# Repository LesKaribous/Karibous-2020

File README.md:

# Karibous-2020
Sources des projets robotique des Karibous pour l'année 2020

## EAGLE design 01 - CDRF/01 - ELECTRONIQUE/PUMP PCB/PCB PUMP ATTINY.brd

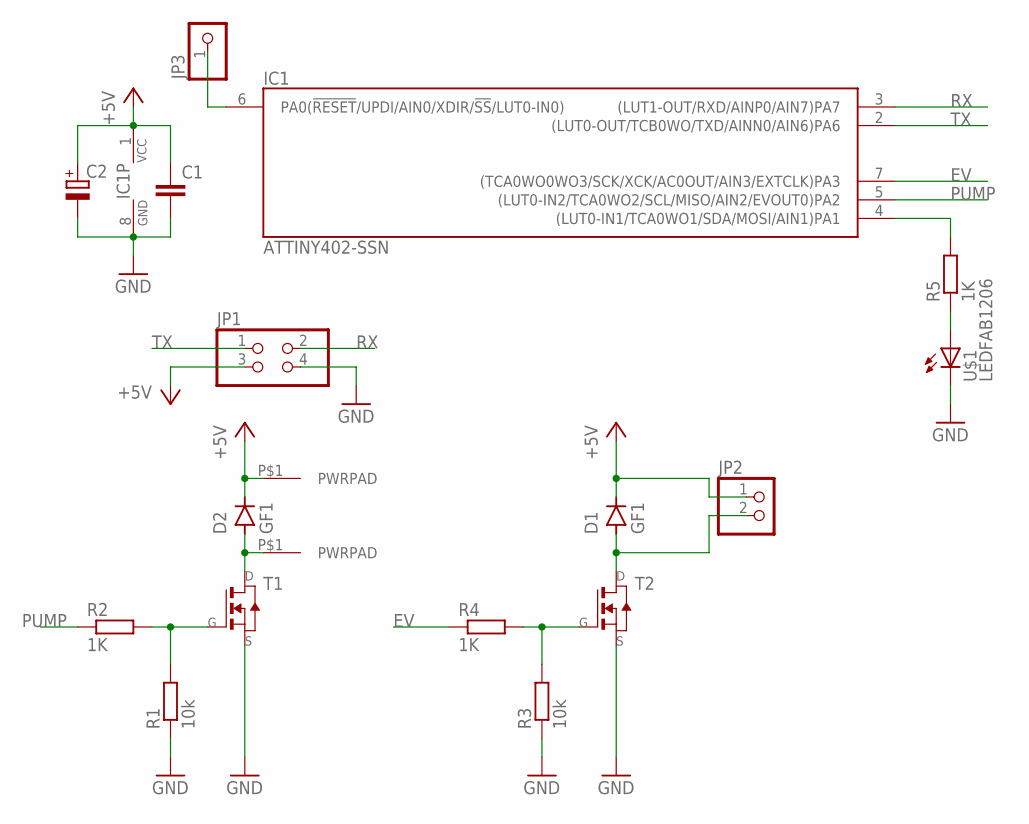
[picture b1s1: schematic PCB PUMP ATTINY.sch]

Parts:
C1: C-EUC1206; C1206
C2: CPOL-EU153CLV-0505; 153CLV-0505
D1, D2: GF1; SMA-DO214AC
IC1: ATTINY402-SSN; SO8
J3, J4: PWRPAD2-5MM; PWRPAD_2-5MM
JP1: PINHD-2X02_2.54-SMD; 2X02SMD
JP2: PINHD-1X02_2.54-SMD-90°; 1X02SMD/90
JP3: PINHD-1X01_2.54-SMD; 1X01SMD
R1, R3: 10k; R1206
R2, R4, R5: 1K; R1206
T1, T2: NMOSFETSOT23; SOT-23
U$1: LEDFAB1206; LED1206FAB

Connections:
+5V: C1.1, C2.+, D1.K (C), D2.K (C), IC1.1 (VCC), J4.P$1, JP1.3, JP2.1
EV: IC1.7 ((TCA0WO0WO3/SCK/XCK/AC0OUT/AIN3/EXTCLK)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), R4.1
GND: C1.2, C2.-, IC1.8 (GND), JP1.4, R1.1, R3.1, T1.2 (S), T2.2 (S), U$1.2 (C)
unnamed: D1.A, JP2.2, T2.1 (D)
unnamed: D2.A, J3.P$1, T1.1 (D)
unnamed: R1.2, R2.2, T1.3 (G)
unnamed: R3.2, R4.2, T2.3 (G)
unnamed: IC1.6 (PA0(!RESET!/UPDI/AIN0/XDIR/!SS!/LUT0-IN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), JP3.1
unnamed: R5.1, U$1.1 (A)
unnamed: IC1.4 ((LUT0-IN1/TCA0WO1/SDA/MOSI/AIN1)PA1), R5.2
PUMP: IC1.5 ((LUT0-IN2/TCA0WO2/SCL/MISO/AIN2/EVOUT0)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), R2.1
RX: IC1.3 ((LUT1-OUT/RXD/AINP0/AIN7)PA7), JP1.2
TX: IC1.2 ((LUT0-OUT/TCB0WO/TXD/AINN0/AIN6)PA6), JP1.1

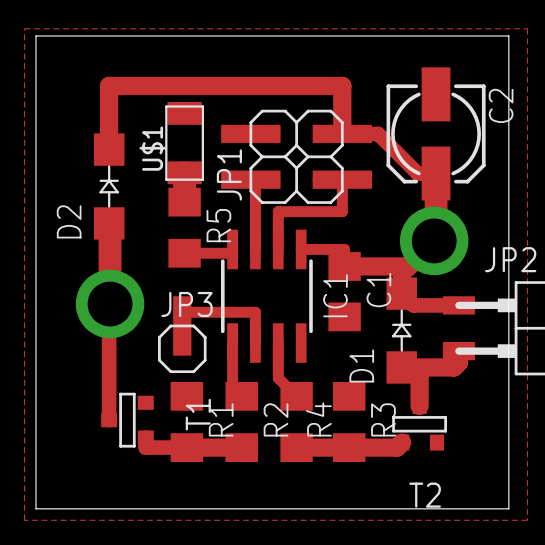
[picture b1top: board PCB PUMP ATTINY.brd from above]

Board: 2 copper layers, 26.3 x 26.3 mm, 18 parts (0 on the bottom side), 13 nets.

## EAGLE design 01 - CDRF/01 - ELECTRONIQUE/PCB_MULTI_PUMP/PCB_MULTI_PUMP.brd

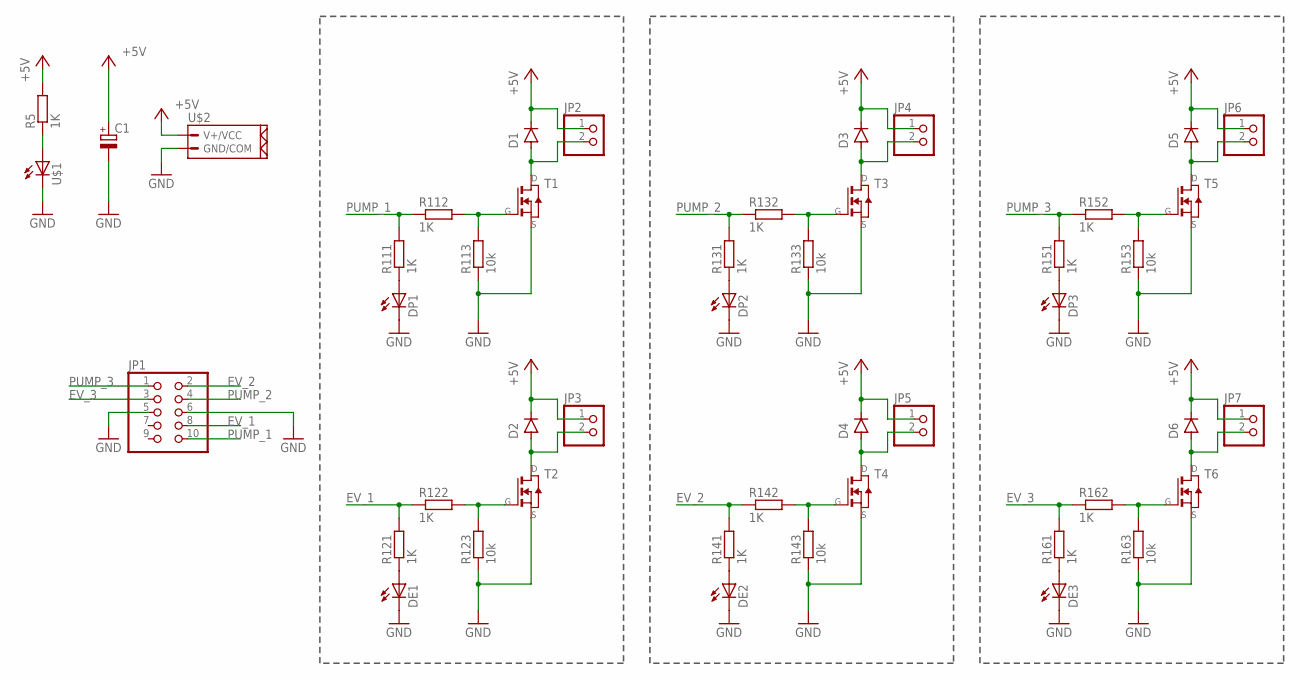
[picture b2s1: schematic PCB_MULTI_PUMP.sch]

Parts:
C1: CPOL-EUE5-10.5; E5-10,5
D1, D2, D3, D4, D5, D6: GF1; SMA-DO214AC
DE1, DE2, DE3: LEDFAB1206; LED1206FAB
DP1, DP2, DP3: LEDFAB1206; LED1206FAB
JP1: PINHD-2X05_2.54-SMD; 2X05SMD
JP2, JP3, JP4, JP5, JP6, JP7: PINHD-1X02_2.54-SMD-90°; 1X02SMD/90
R5, R111, R112, R121, R122, R131, R132, R141, R142, R151, R152, R161, R162: 1K; R1206
R113, R123, R133, R143, R153, R163: 10k; R1206
T1, T2, T3, T4, T5, T6: NMOSFETSOT23; SOT-23
U$1: LEDFAB1206; LED1206FAB
U$2: CONN_02_PUI; NSK396-2C

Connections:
+5V: C1.+, D1.K (C), D2.K (C), D3.K (C), D4.K (C), D5.K (C), D6.K (C), JP2.1, JP3.1, JP4.1, JP5.1, JP6.1, JP7.1, R5.2, U$2.P$2 (V+/VCC)
EV_1: JP1.8, R121.2, R122.1
EV_2: JP1.2, R141.2, R142.1
EV_3: JP1.3, R161.2, R162.1
GND: C1.-, DE1.2 (C), DE2.2 (C), DE3.2 (C), DP1.2 (C), DP2.2 (C), DP3.2 (C), JP1.5, JP1.6, R113.1, R123.1, R133.1, R143.1, R153.1, R163.1, T1.2 (S), T2.2 (S), T3.2 (S), T4.2 (S), T5.2 (S), T6.2 (S), U$1.2 (C), U$2.P$1 (GND/COM)
unnamed: D2.A, JP3.2, T2.1 (D)
unnamed: D1.A, JP2.2, T1.1 (D)
unnamed: R112.2, R113.2, T1.3 (G)
unnamed: R122.2, R123.2, T2.3 (G)
unnamed: R5.1, U$1.1 (A)
unnamed: DP1.1 (A), R111.1
unnamed: DE1.1 (A), R121.1
unnamed: D3.A, JP4.2, T3.1 (D)
unnamed: R132.2, R133.2, T3.3 (G)
unnamed: D4.A, JP5.2, T4.1 (D)
unnamed: R142.2, R143.2, T4.3 (G)
unnamed: DP2.1 (A), R131.1
unnamed: DE2.1 (A), R141.1
unnamed: D5.A, JP6.2, T5.1 (D)
unnamed: R152.2, R153.2, T5.3 (G)
unnamed: D6.A, JP7.2, T6.1 (D)
unnamed: R162.2, R163.2, T6.3 (G)
unnamed: DP3.1 (A), R151.1
unnamed: DE3.1 (A), R161.1
PUMP_1: JP1.10, R111.2, R112.1
PUMP_2: JP1.4, R131.2, R132.1
PUMP_3: JP1.1, R151.2, R152.1

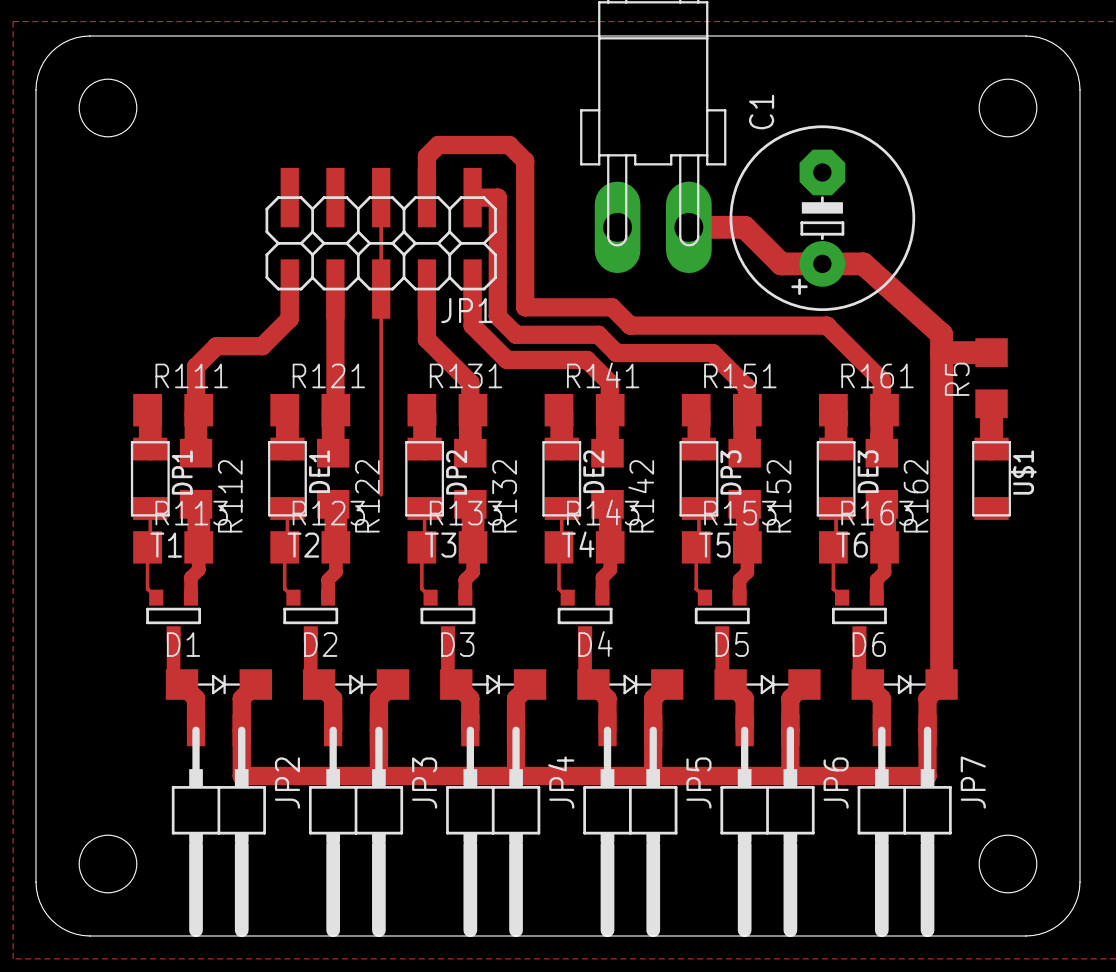
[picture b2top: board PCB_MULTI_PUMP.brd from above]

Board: 2 copper layers, 58.0 x 50.0 mm, 47 parts (0 on the bottom side), 27 nets.

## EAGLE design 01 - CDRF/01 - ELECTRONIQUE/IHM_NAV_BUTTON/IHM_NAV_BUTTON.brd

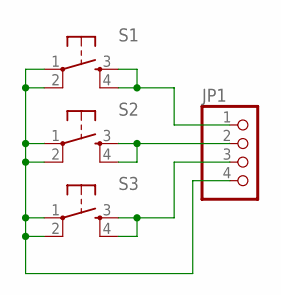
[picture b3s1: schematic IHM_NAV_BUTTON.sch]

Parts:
JP1: PINHD-1X04_2.54-SMD-90°; 1X04SMD/90
S1, S2, S3: 6MM_SWITCH6MM_SWITCH; 6MM_SWITCH

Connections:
unnamed: JP1.1, S1.3 (S), S1.4 (S1)
unnamed: JP1.2, S2.3 (S), S2.4 (S1)
unnamed: JP1.3, S3.3 (S), S3.4 (S1)
unnamed: JP1.4, S1.1, S1.2 (P1), S2.1, S2.2 (P1), S3.1, S3.2 (P1)

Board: 2 copper layers, 4 parts (0 on the bottom side), 4 nets, no tracks yet.

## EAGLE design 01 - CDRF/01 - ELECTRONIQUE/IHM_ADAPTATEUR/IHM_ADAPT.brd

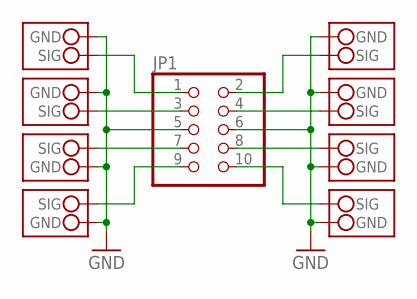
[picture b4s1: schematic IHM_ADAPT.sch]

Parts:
JP1: PINHD-2X05_2.54-SMD; 2X05SMD
U$1, U$2, U$3, U$4, U$5, U$6, U$7, U$8: CONN_WIRE; SMD_WIRE_CON

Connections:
GND: JP1.5, JP1.6, U$1.P$1 (GND), U$2.P$1 (GND), U$3.P$1 (GND), U$4.P$1 (GND), U$5.P$1 (GND), U$6.P$1 (GND), U$7.P$1 (GND), U$8.P$1 (GND)
unnamed: JP1.10, U$4.P$2 (SIG)
unnamed: JP1.8, U$2.P$2 (SIG)
unnamed: JP1.4, U$1.P$2 (SIG)
unnamed: JP1.2, U$3.P$2 (SIG)
unnamed: JP1.9, U$8.P$2 (SIG)
unnamed: JP1.7, U$6.P$2 (SIG)
unnamed: JP1.3, U$5.P$2 (SIG)
unnamed: JP1.1, U$7.P$2 (SIG)

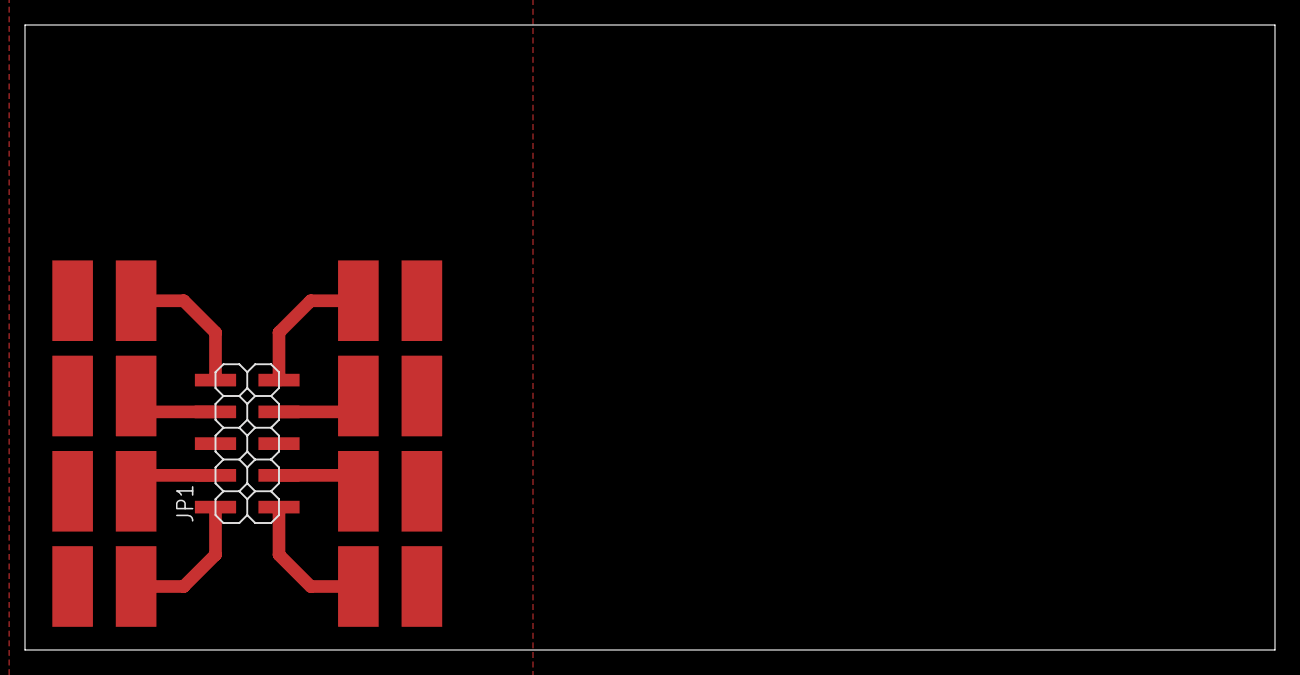
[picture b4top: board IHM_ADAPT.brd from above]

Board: 2 copper layers, 100.0 x 50.0 mm, 9 parts (0 on the bottom side), 9 nets.

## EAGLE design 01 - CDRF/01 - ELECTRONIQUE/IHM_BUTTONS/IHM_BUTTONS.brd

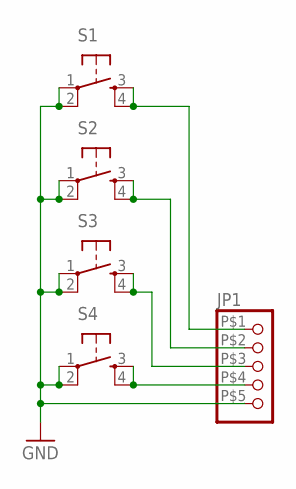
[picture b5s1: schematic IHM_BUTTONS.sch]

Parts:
JP1: PINHD-1X05_2.54-SMD-WIRE; 1X05WIRE
S1, S2, S3, S4: 6MM_SWITCH6MM_SWITCH; 6MM_SWITCH

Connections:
GND: JP1.P$5 (5), S1.1, S1.2 (P1), S2.1, S2.2 (P1), S3.1, S3.2 (P1), S4.1, S4.2 (P1)
unnamed: JP1.P$4 (4), S4.3 (S), S4.4 (S1)
unnamed: JP1.P$3 (3), S3.3 (S), S3.4 (S1)
unnamed: JP1.P$2 (2), S2.3 (S), S2.4 (S1)
unnamed: JP1.P$1 (1), S1.3 (S), S1.4 (S1)

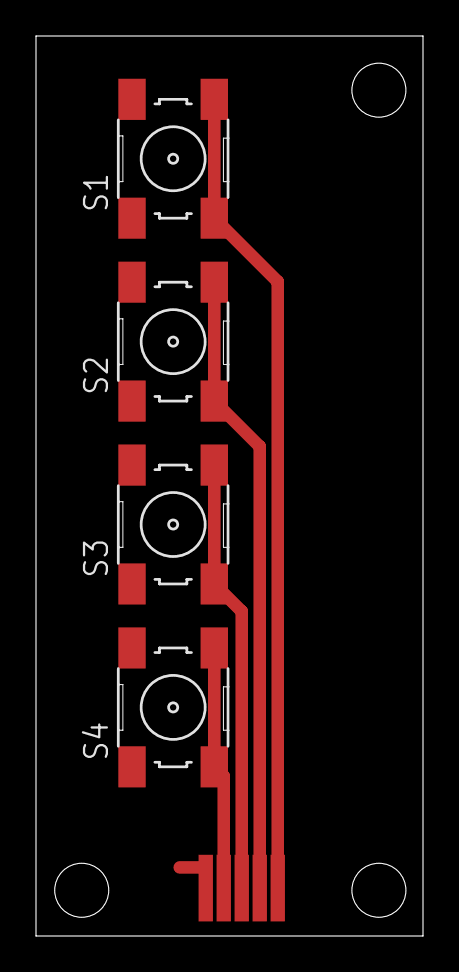
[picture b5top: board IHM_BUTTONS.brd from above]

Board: 2 copper layers, 21.5 x 50.0 mm, 5 parts (0 on the bottom side), 5 nets.

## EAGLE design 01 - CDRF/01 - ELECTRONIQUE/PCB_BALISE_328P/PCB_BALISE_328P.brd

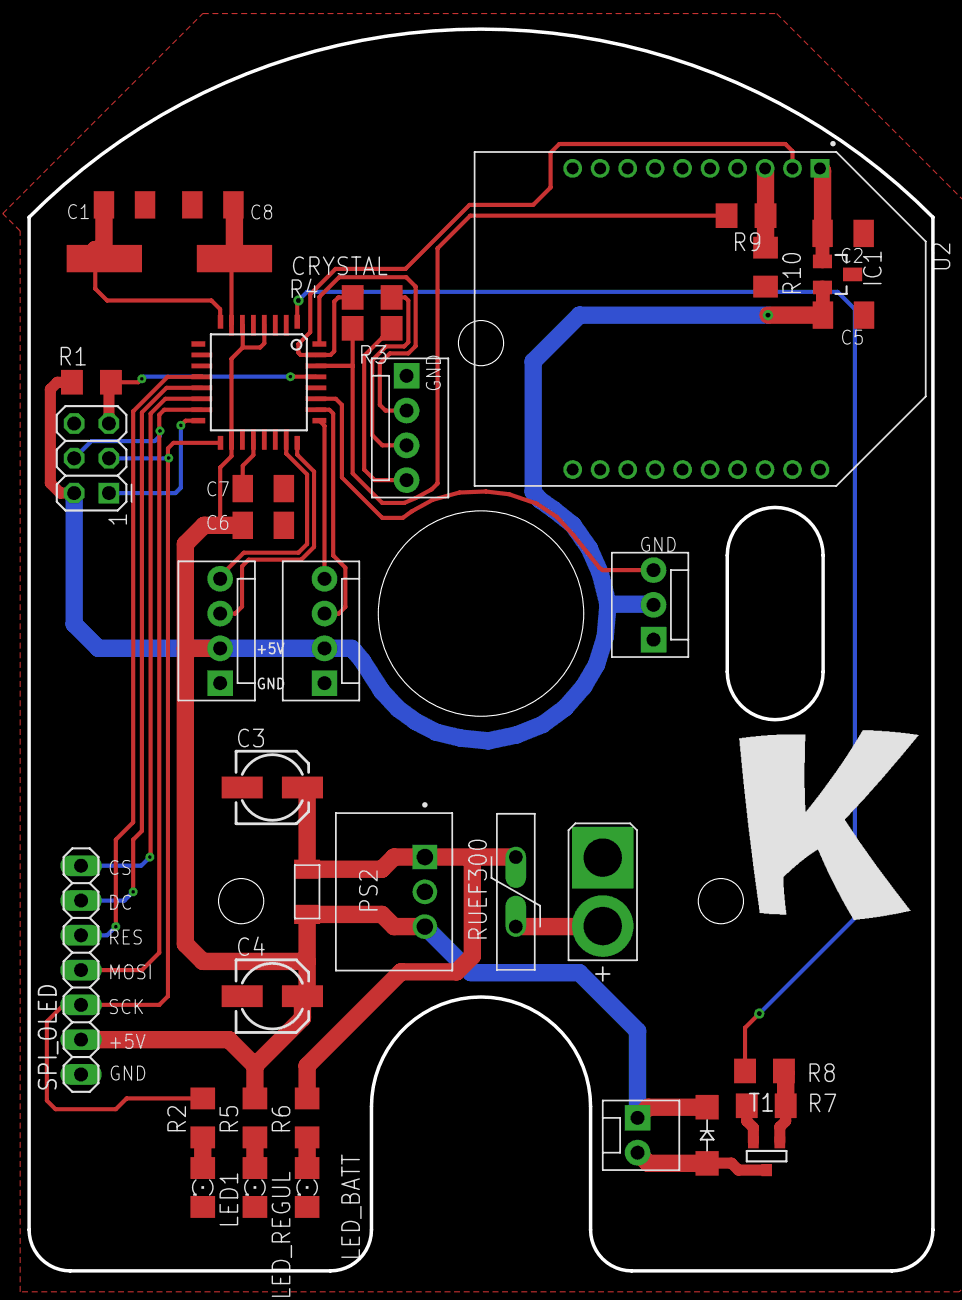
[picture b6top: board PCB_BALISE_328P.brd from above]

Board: 2 copper layers, 66.0 x 90.7 mm, 39 parts (0 on the bottom side), 32 nets.

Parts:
C1, C8: 22pF; C1206K
C2, C5: C1206K
C3, C4: 10uF; 153CLV-0505
C6, C7: 0,1uF; C1206K
CRYSTAL: 16Mhz; CSM-7X-DU
D1: M7; MINI-SMA
D2: GF1; SMA-DO214AC
IC1: SOT23
J1, J3, J4: MOLEX-1X4
J2: MOLEX-1X2
J5: MOLEX-1X3
LED1: 1206
LED_BATT: LED_1206
LED_REGUL: LED_1206
MICRO: ATMEGA328P-AU; TQFP32-08
PS2: R-78B5.0-2.0; CONV_R-78B5.0-2.0
R1, R8: 1K; R1206
R2, R5, R6, R9, R10: R1206
R3, R4: 1k; R1206
R7: 10k; R1206
RU1: RUEF300
SPI_OLED: 1X07
T1: SOT-23
U1: AVRISP; 2X03
U2: XBP24CAUIT-001; MODULE_XBP24CAUIT-001
U$1: LOGO_K; LOGO_KARIBOU
U$5: CONN_02_PUIXT30; XT30_FEMALE

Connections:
+5V: C4.+, C5.2, C6.1, D1.ANODE, D2.K, IC1.2, J2.1, J3.2, J4.2, J5.2, MICRO.4, MICRO.6, MICRO.18, PS2.3, R1.2, R5.2, SPI_OLED.2, U1.2
CAPT_1: J3.4, MICRO.23
CAPT_2: J3.3, MICRO.24
CAPT_3: J4.4, MICRO.25
CAPT_4: J4.3, MICRO.26
CS: MICRO.14, SPI_OLED.7
DC: MICRO.13, SPI_OLED.6
GND: C1.1, C2.1, C3.-, C4.-, C5.1, C6.2, C7.2, C8.1, IC1.3, J1.1, J3.1, J4.1, J5.1, LED1.C, LED_BATT.C, LED_REGUL.C, MICRO.3, MICRO.5, MICRO.21, PS2.2, R7.1, R10.2, SPI_OLED.1, T1.2, U1.6, U2.10, U$5.P$2
HALL_SENSOR: J5.3, MICRO.27
MISO: MICRO.16, U1.1
MOSI: MICRO.15, SPI_OLED.4, U1.4
unnamed: C7.1, MICRO.20
unnamed: C8.2, CRYSTAL.2, MICRO.7
unnamed: LED1.A, R2.1
unnamed: C2.2, IC1.1, U2.1
unnamed: J1.2, MICRO.32
unnamed: LED_BATT.A, R6.1
unnamed: RU1.P$1, U$5.P$1
unnamed: C1.2, CRYSTAL.1, MICRO.8
unnamed: LED_REGUL.A, R5.1
unnamed: D2.A, J2.2, T1.1
unnamed: R7.2, R8.2, T1.3
unnamed: MICRO.1, R8.1
unnamed: R9.1, R10.1, U2.3
RES: MICRO.12, SPI_OLED.5
RST: MICRO.29, R1.1, U1.5
RX: J1.3, R4.1
RX_RAW: MICRO.31, R4.2, U2.2
SCK: MICRO.17, R2.2, SPI_OLED.3, U1.3
TX: J1.4, R3.1
TX_RAW: MICRO.30, R3.2, R9.2
VIN/BATT: C3.+, D1.KATHODE, PS2.1, R6.2, RU1.P$2

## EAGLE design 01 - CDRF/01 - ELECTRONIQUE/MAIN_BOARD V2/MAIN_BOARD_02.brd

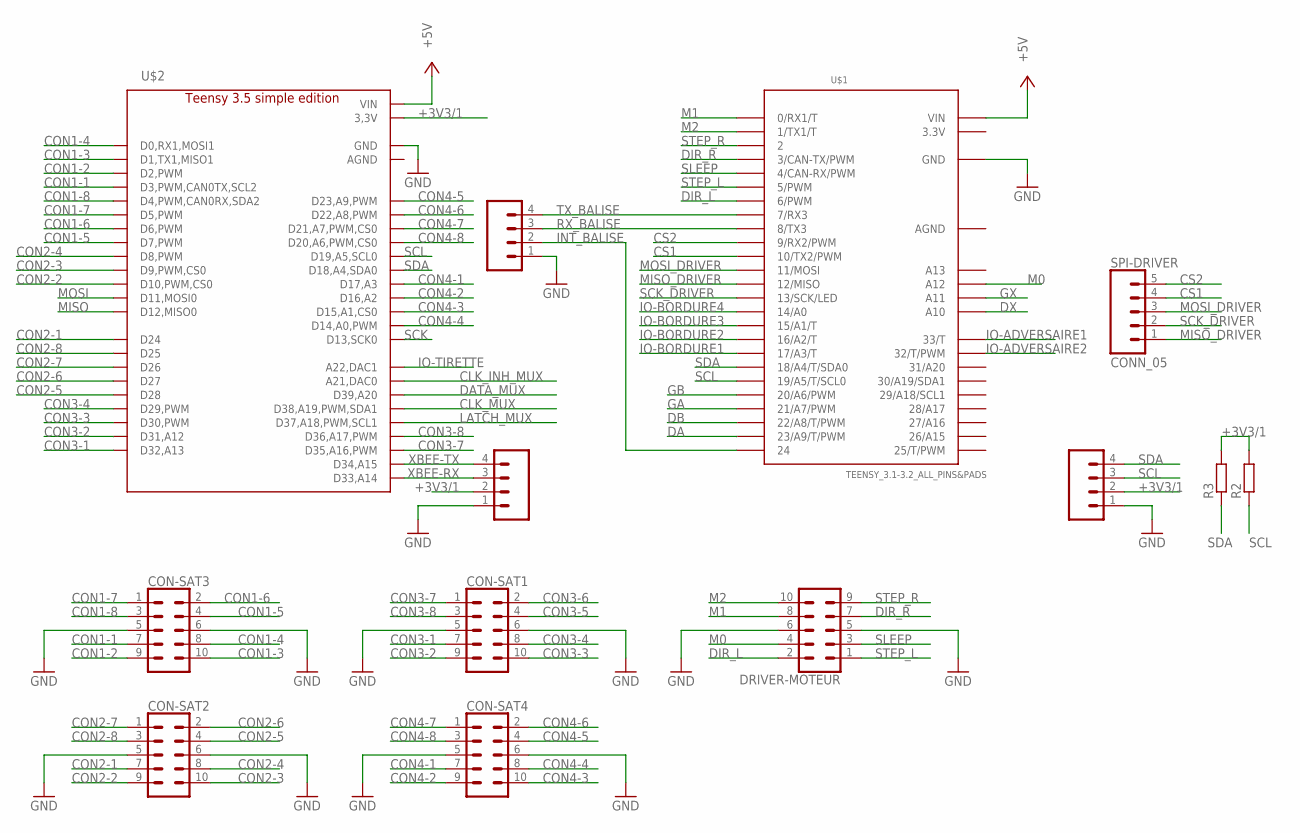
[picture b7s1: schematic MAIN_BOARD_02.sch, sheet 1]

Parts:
COM-BALISE: CONN_04POLAR; MOLEX-1X4
COM-I2C: CONN_04POLAR; MOLEX-1X4
COM-XBEE: CONN_04POLAR; MOLEX-1X4
CON-SAT1, CON-SAT2, CON-SAT3, CON-SAT4: CONN_05X2SHD; 2X5-SHROUDED
DRIVER-MOTEUR: CONN_05X2SHD; 2X5-SHROUDED
R2, R3: R-EU_R1206; R1206
SPI-DRIVER: CONN_05; MOLEX-1X5
U$1: TEENSY_3.1-3.2_ALL_PINS&PADS; TEENSY_3.0-3.2_ALL_PINS_&_PADS
U$2: TEENSY_3.5; TEENSY_3.5_LIGHT

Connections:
3.3V: U$1.3.3V, U$1.3.3V2 (3.3V)
+3V3/1: COM-I2C.2, COM-XBEE.2, R2.2, R3.2, U$2.P$15 (3,3V), U$2.P$46 (3,3V)
+5V: U$1.VIN, U$2.P$48 (VIN); also elsewhere on the board
AGND: U$1.AGND
CLK_INH_MUX: U$2.P$32 (A21,DAC0); also elsewhere on the board
CLK_MUX: U$2.P$30 (D38,A19,PWM,SDA1); also elsewhere on the board
CON1-1: CON-SAT3.7, U$2.P$5 (D3,PWM,CAN0TX,SCL2)
CON1-2: CON-SAT3.9, U$2.P$4 (D2,PWM)
CON1-3: CON-SAT3.10, U$2.P$3 (D1,TX1,MISO1)
CON1-4: CON-SAT3.8, U$2.P$2 (D0,RX1,MOSI1)
CON1-5: CON-SAT3.4, U$2.P$9 (D7,PWM)
CON1-6: CON-SAT3.2, U$2.P$8 (D6,PWM)
CON1-7: CON-SAT3.1, U$2.P$7 (D5,PWM)
CON1-8: CON-SAT3.3, U$2.P$6 (D4,PWM,CAN0RX,SDA2)
CON2-1: CON-SAT2.7, U$2.P$16 (D24)
CON2-2: CON-SAT2.9, U$2.P$12 (D10,PWM,CS0)
CON2-3: CON-SAT2.10, U$2.P$11 (D9,PWM,CS0)
CON2-4: CON-SAT2.8, U$2.P$10 (D8,PWM)
CON2-5: CON-SAT2.4, U$2.P$20 (D28)
CON2-6: CON-SAT2.2, U$2.P$19 (D27)
CON2-7: CON-SAT2.1, U$2.P$18 (D26)
CON2-8: CON-SAT2.3, U$2.P$17 (D25)
CON3-1: CON-SAT1.7, U$2.P$24 (D32,A13)
CON3-2: CON-SAT1.9, U$2.P$23 (D31,A12)
CON3-3: CON-SAT1.10, U$2.P$22 (D30,PWM)
CON3-4: CON-SAT1.8, U$2.P$21 (D29,PWM)
CON3-5: CON-SAT1.4
CON3-6: CON-SAT1.2
CON3-7: CON-SAT1.1, U$2.P$27 (D35,A16,PWM)
CON3-8: CON-SAT1.3, U$2.P$28 (D36,A17,PWM)
CON4-1: CON-SAT4.7, U$2.P$39 (D17,A3)
CON4-2: CON-SAT4.9, U$2.P$38 (D16,A2)
CON4-3: CON-SAT4.10, U$2.P$37 (D15,A1,CS0)
CON4-4: CON-SAT4.8, U$2.P$36 (D14,A0,PWM)
CON4-5: CON-SAT4.4, U$2.P$45 (D23,A9,PWM)
CON4-6: CON-SAT4.2, U$2.P$44 (D22,A8,PWM)
CON4-7: CON-SAT4.1, U$2.P$43 (D21,A7,PWM,CS0)
CON4-8: CON-SAT4.3, U$2.P$42 (D20,A6,PWM,CS0)
CS1: SPI-DRIVER.4, U$1.10 (10/TX2/PWM)
CS2: SPI-DRIVER.5, U$1.9 (9/RX2/PWM)
DA: U$1.23/A9 (23/A9/T/PWM); also elsewhere on the board
DATA_MUX: U$2.P$31 (D39,A20); also elsewhere on the board
DB: U$1.22/A8 (22/A8/T/PWM); also elsewhere on the board
DIR_L: DRIVER-MOTEUR.2, U$1.6 (6/PWM)
DIR_R: DRIVER-MOTEUR.7, U$1.3 (3/CAN-TX/PWM)
DX: U$1.A10; also elsewhere on the board
GA: U$1.21/A7 (21/A7/PWM); also elsewhere on the board
GB: U$1.20/A6 (20/A6/PWM); also elsewhere on the board
GND: COM-BALISE.1, COM-I2C.1, COM-XBEE.1, CON-SAT1.5, CON-SAT1.6, CON-SAT2.5, CON-SAT2.6, CON-SAT3.5, CON-SAT3.6, CON-SAT4.5, CON-SAT4.6, DRIVER-MOTEUR.5, DRIVER-MOTEUR.6, U$1.GND, U$1.GND2 (GND), U$2.GND, U$2.P$34 (GND); also elsewhere on the board
GX: U$1.A11; also elsewhere on the board
INT_BALISE: COM-BALISE.2, U$1.24
IO-ADVERSAIRE1: U$1.33 (33/T); also elsewhere on the board
IO-ADVERSAIRE2: U$1.32 (32/T/PWM); also elsewhere on the board
IO-BORDURE1: U$1.17/A3 (17/A3/T); also elsewhere on the board
IO-BORDURE2: U$1.16/A2 (16/A2/T); also elsewhere on the board
IO-BORDURE3: U$1.15/A1 (15/A1/T); also elsewhere on the board
IO-BORDURE4: U$1.14/A0; also elsewhere on the board
IO-TIRETTE: U$2.P$33 (A22,DAC1); also elsewhere on the board
LATCH_MUX: U$2.P$29 (D37,A18,PWM,SCL1); also elsewhere on the board
M0: DRIVER-MOTEUR.4, U$1.A12
M1: DRIVER-MOTEUR.8, U$1.0 (0/RX1/T)
M2: DRIVER-MOTEUR.10, U$1.1 (1/TX1/T)
MISO: U$2.P$14 (D12,MISO0); also elsewhere on the board
MISO_DRIVER: SPI-DRIVER.1, U$1.12 (12/MISO)
MOSI: U$2.P$13 (D11,MOSI0); also elsewhere on the board
MOSI_DRIVER: SPI-DRIVER.3, U$1.11 (11/MOSI)
RX_BALISE: COM-BALISE.3, U$1.8 (8/TX3)
SCK: U$2.P$35 (D13,SCK0); also elsewhere on the board
SCK_DRIVER: SPI-DRIVER.2, U$1.13 (13/SCK/LED)
SCL: COM-I2C.3, R2.1, U$1.19/A5 (19/A5/T/SCL0), U$2.P$41 (D19,A5,SCL0)
SDA: COM-I2C.4, R3.1, U$1.18/A4 (18/A4/T/SDA0), U$2.P$40 (D18,A4,SDA0)
SLEEP: DRIVER-MOTEUR.3, U$1.4 (4/CAN-RX/PWM)
STEP_L: DRIVER-MOTEUR.1, U$1.5 (5/PWM)
STEP_R: DRIVER-MOTEUR.9, U$1.2
TX_BALISE: COM-BALISE.4, U$1.7 (7/RX3)
XBEE-RX: COM-XBEE.3, U$2.P$25 (D33,A14)
XBEE-TX: COM-XBEE.4, U$2.P$26 (D34,A15)

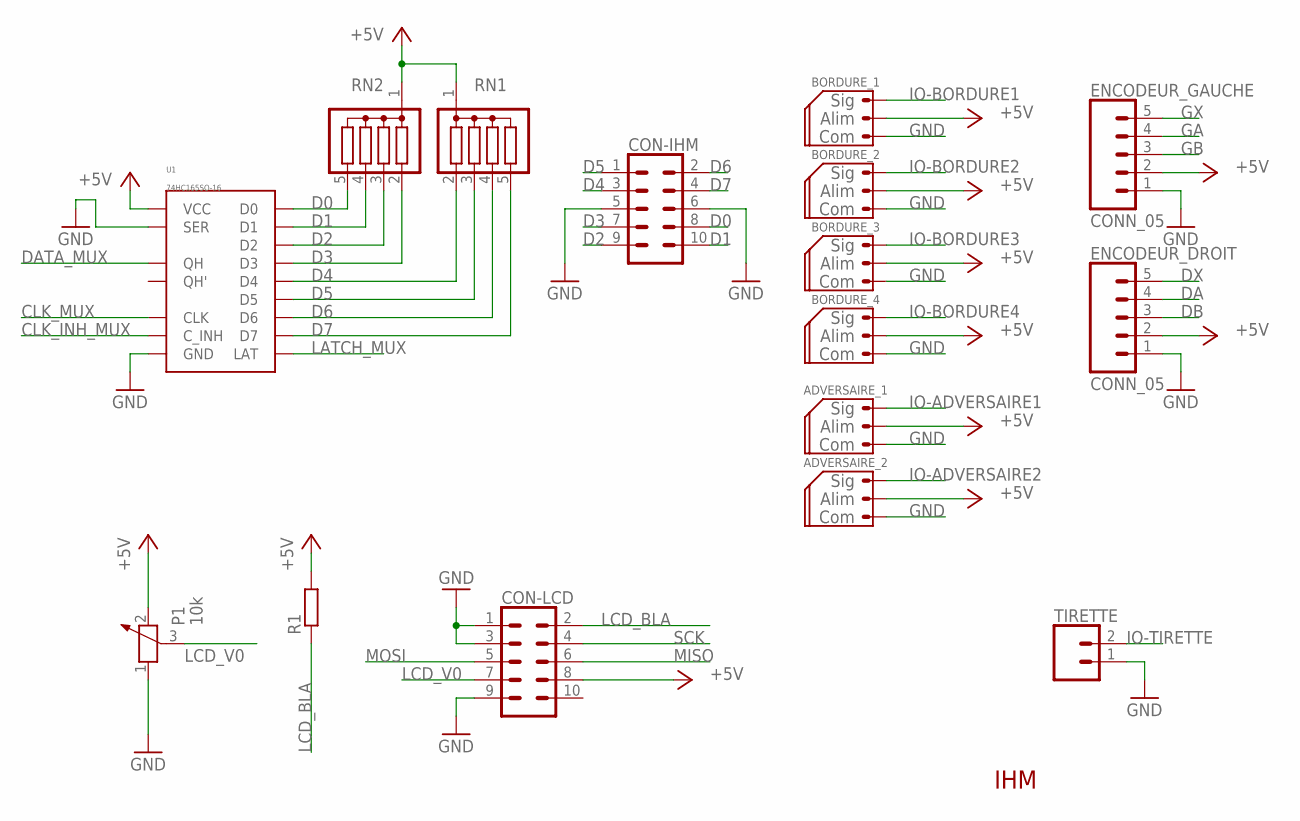
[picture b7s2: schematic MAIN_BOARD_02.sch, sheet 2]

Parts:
ADVERSAIRE_1, ADVERSAIRE_2: CONN_03_SERVO; MOLEX-1X3
BORDURE_1, BORDURE_2, BORDURE_3, BORDURE_4: CONN_03_SERVO; MOLEX-1X3
CON-IHM: CONN_05X2SHD; 2X5-SHROUDED
CON-LCD: CONN_05X2SHD; 2X5-SHROUDED
ENCODEUR_DROIT: CONN_05; MOLEX-1X5
ENCODEUR_GAUCHE: CONN_05; MOLEX-1X5
P1: 10k; PT-10
R1: R-EU_R1206; R1206
RN1, RN2: G04R; SIL5
TIRETTE: CONN_02POLAR; MOLEX-1X2
U1: 74HC165SO-16; SO-16
U$3: LOGO_K; LOGO_KARIBOU

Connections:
+5V: ADVERSAIRE_1.2, ADVERSAIRE_2.2, BORDURE_1.2, BORDURE_2.2, BORDURE_3.2, BORDURE_4.2, CON-LCD.8, ENCODEUR_DROIT.2, ENCODEUR_GAUCHE.2, P1.2, R1.2, RN1.1, RN2.1, U1.16 (VCC); also elsewhere on the board
CLK_INH_MUX: U1.15 (C_INH); also elsewhere on the board
CLK_MUX: U1.2 (CLK); also elsewhere on the board
D0: CON-IHM.8, RN2.5, U1.11 (D0)
D1: CON-IHM.10, RN2.4, U1.12 (D1)
D2: CON-IHM.9, RN2.3, U1.13 (D2)
D3: CON-IHM.7, RN2.2, U1.14 (D3)
D4: CON-IHM.3, RN1.2, U1.3 (D4)
D5: CON-IHM.1, RN1.3, U1.4 (D5)
D6: CON-IHM.2, RN1.4, U1.5 (D6)
D7: CON-IHM.4, RN1.5, U1.6 (D7)
DA: ENCODEUR_DROIT.4; also elsewhere on the board
DATA_MUX: U1.9 (QH); also elsewhere on the board
DB: ENCODEUR_DROIT.3; also elsewhere on the board
DX: ENCODEUR_DROIT.5; also elsewhere on the board
GA: ENCODEUR_GAUCHE.4; also elsewhere on the board
GB: ENCODEUR_GAUCHE.3; also elsewhere on the board
GND: ADVERSAIRE_1.1, ADVERSAIRE_2.1, BORDURE_1.1, BORDURE_2.1, BORDURE_3.1, BORDURE_4.1, CON-IHM.5, CON-IHM.6, CON-LCD.1, CON-LCD.3, CON-LCD.9, ENCODEUR_DROIT.1, ENCODEUR_GAUCHE.1, P1.1, TIRETTE.1, U1.8 (GND), U1.10 (SER); also elsewhere on the board
GX: ENCODEUR_GAUCHE.5; also elsewhere on the board
IO-ADVERSAIRE1: ADVERSAIRE_1.3; also elsewhere on the board
IO-ADVERSAIRE2: ADVERSAIRE_2.3; also elsewhere on the board
IO-BORDURE1: BORDURE_1.3; also elsewhere on the board
IO-BORDURE2: BORDURE_2.3; also elsewhere on the board
IO-BORDURE3: BORDURE_3.3; also elsewhere on the board
IO-BORDURE4: BORDURE_4.3; also elsewhere on the board
IO-TIRETTE: TIRETTE.2; also elsewhere on the board
LATCH_MUX: U1.1 (LAT); also elsewhere on the board
LCD_BLA: CON-LCD.2, R1.1
LCD_V0: CON-LCD.7, P1.3
MISO: CON-LCD.6; also elsewhere on the board
MOSI: CON-LCD.5; also elsewhere on the board
SCK: CON-LCD.4; also elsewhere on the board

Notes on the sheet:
IHM

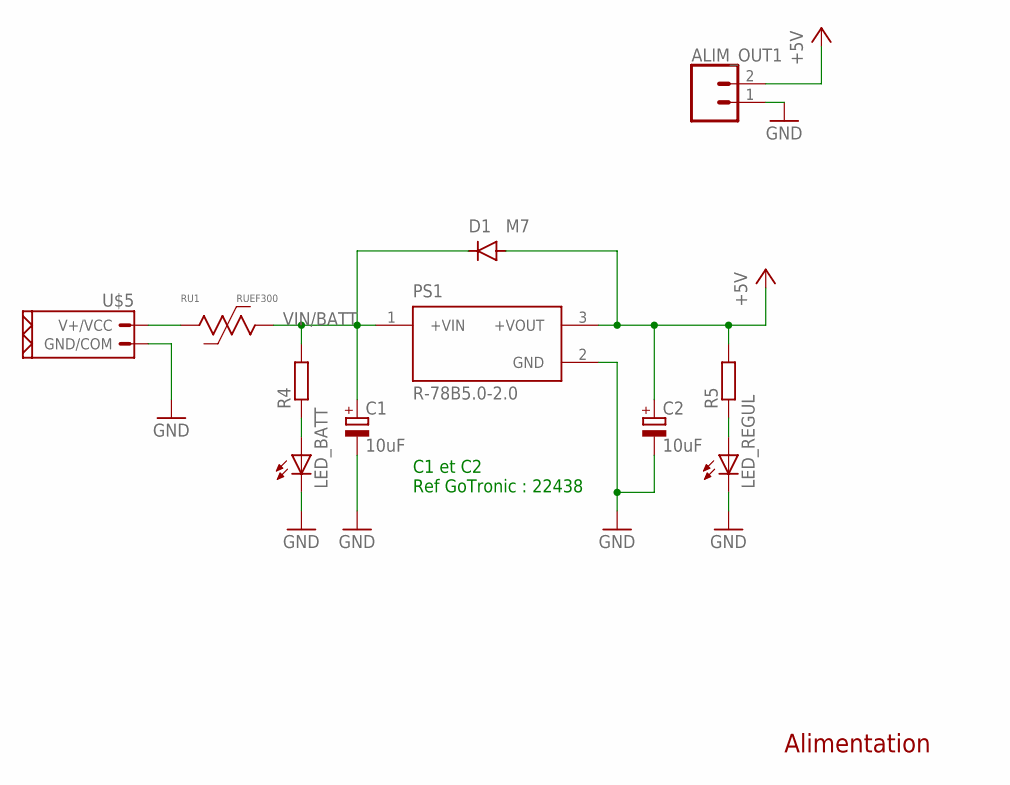
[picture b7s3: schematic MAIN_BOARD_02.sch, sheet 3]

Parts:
ALIM_OUT1: CONN_02POLAR; MOLEX-1X2
C1, C2: 10uF; 153CLV-0505
D1: M7; MINI-SMA
LED_BATT: LED_E; LED_1206
LED_REGUL: LED_E; LED_1206
PS1: R-78B5.0-2.0; CONV_R-78B5.0-2.0
R4, R5: R-EU_R1206; R1206
RU1: RUEF300
U$4: LOGO_K; LOGO_KARIBOU
U$5: CONN_02_PUIXT30; XT30_FEMALE

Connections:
+5V: ALIM_OUT1.2, C2.+, D1.ANODE, PS1.3 (+VOUT), R5.2; also elsewhere on the board
GND: ALIM_OUT1.1, C1.-, C2.-, LED_BATT.C, LED_REGUL.C, PS1.2 (GND), U$5.P$2 (GND/COM); also elsewhere on the board
unnamed: LED_REGUL.A, R5.1
unnamed: LED_BATT.A, R4.1
unnamed: RU1.P$1, U$5.P$1 (V+/VCC)
VIN/BATT: C1.+, D1.KATHODE, PS1.1 (+VIN), R4.2, RU1.P$2

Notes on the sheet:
Alimentation
C1 et C2 Ref GoTronic : 22438

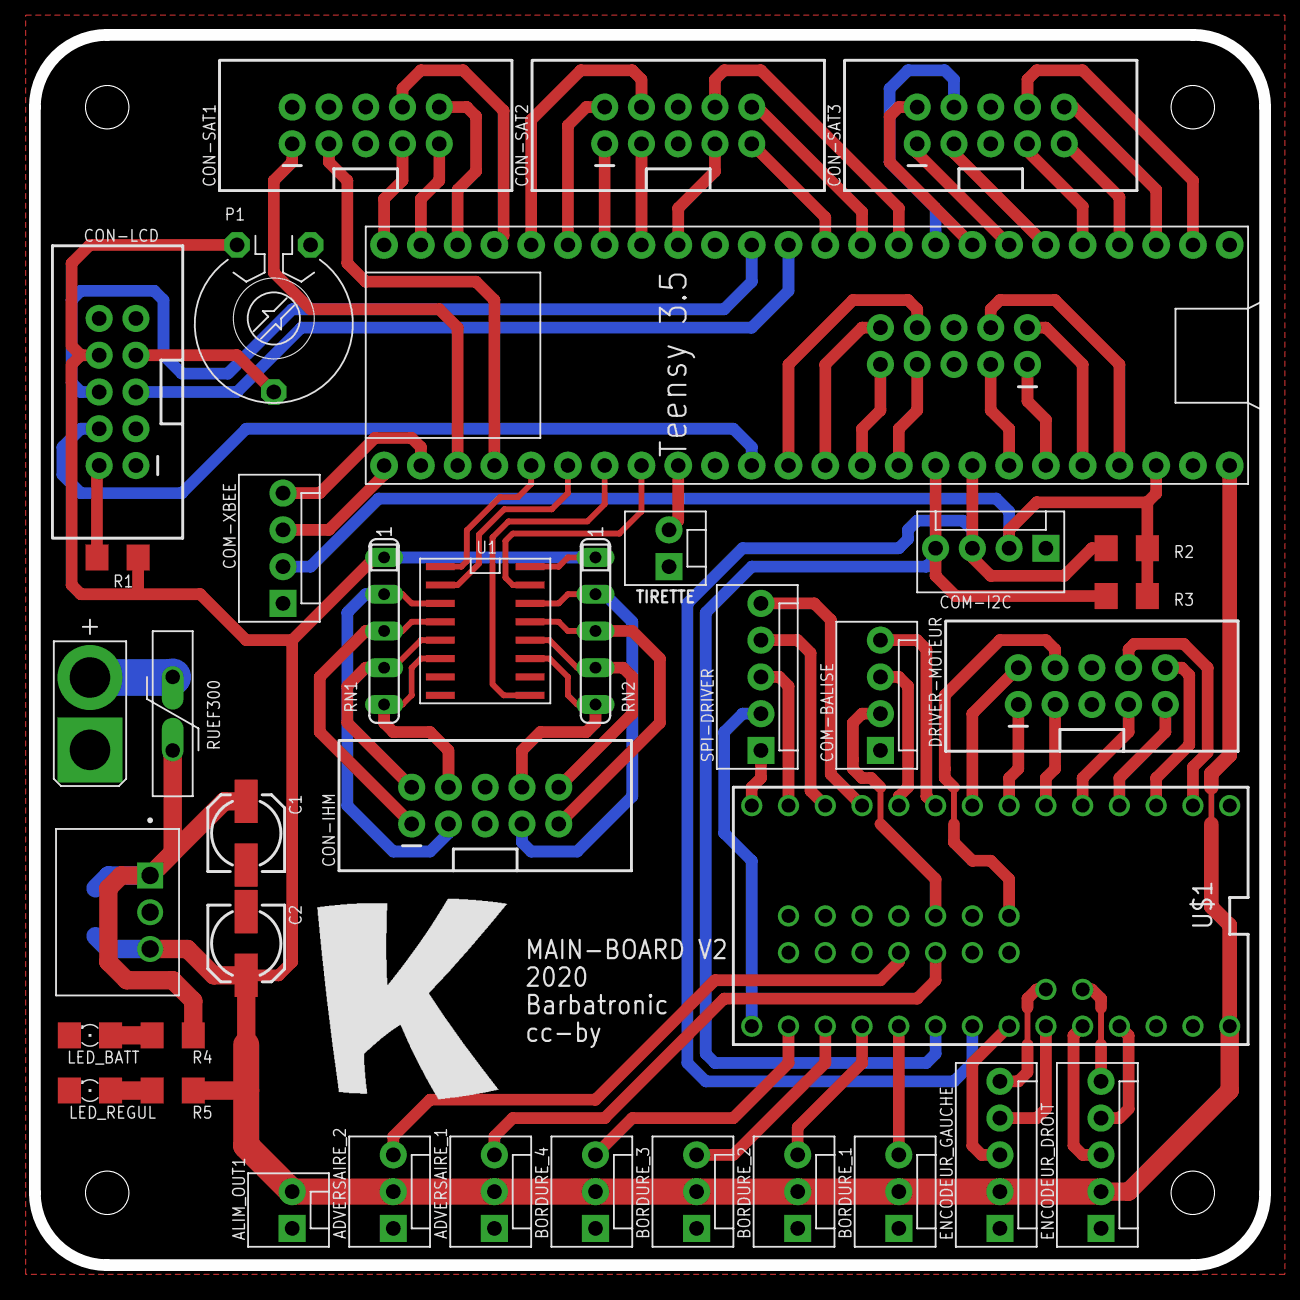
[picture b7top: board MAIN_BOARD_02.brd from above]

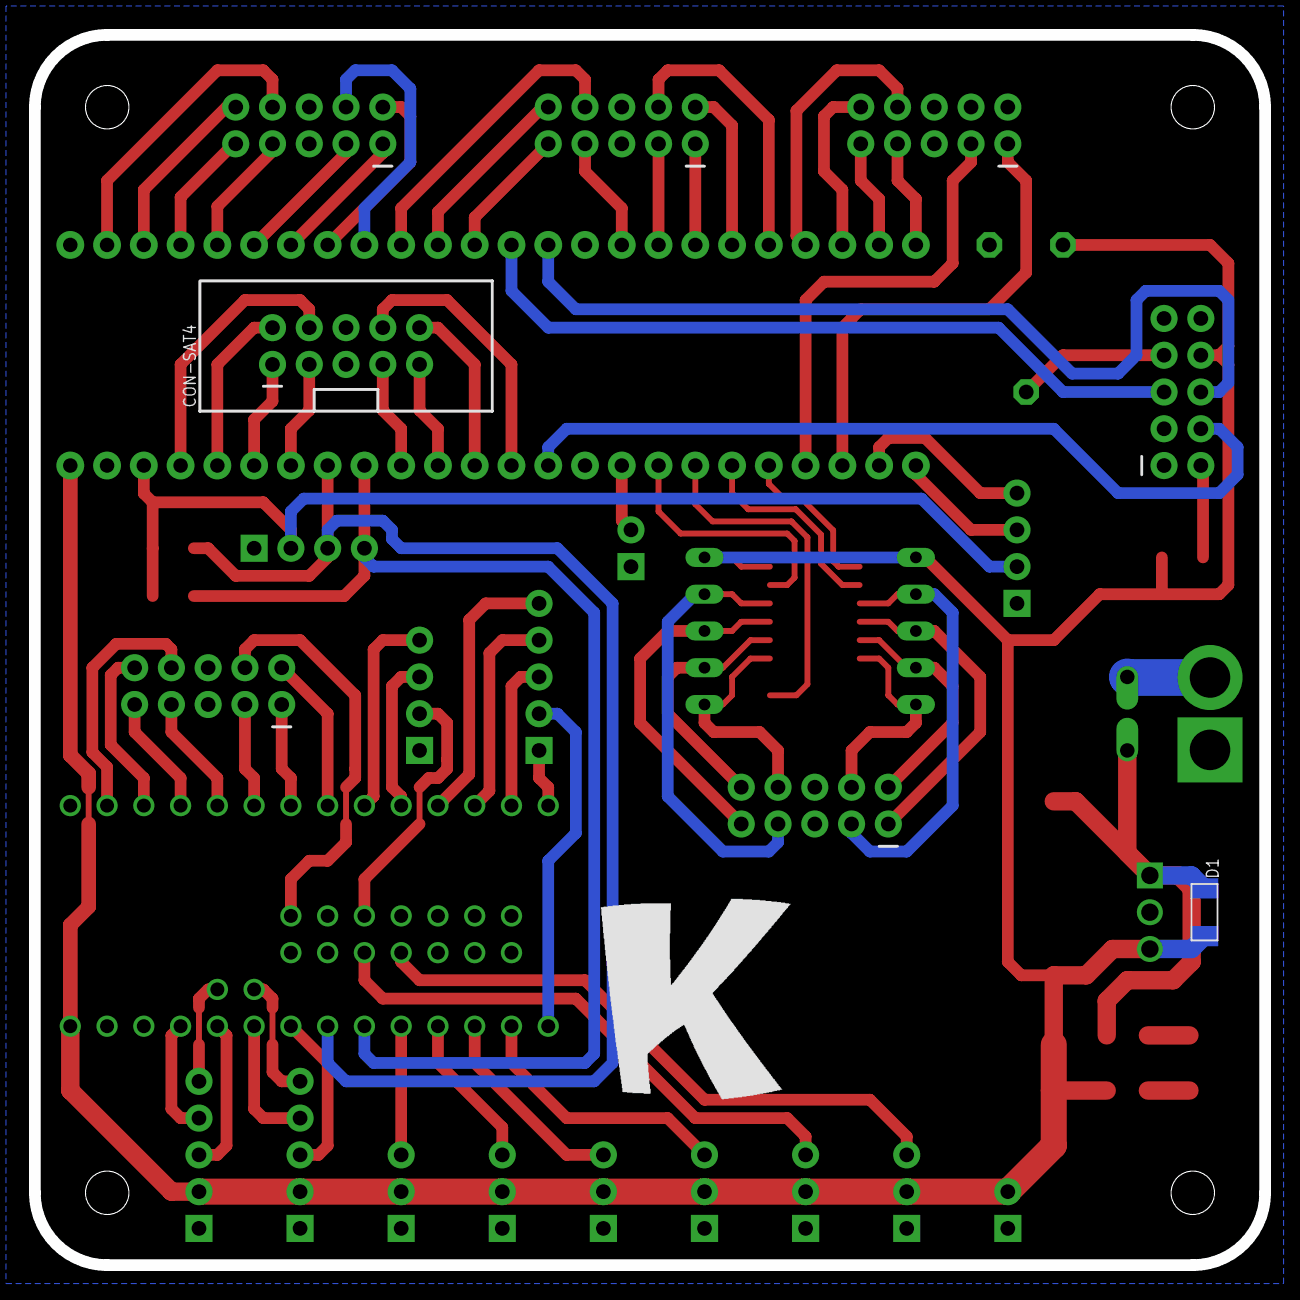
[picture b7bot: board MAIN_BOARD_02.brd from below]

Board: 2 copper layers, 85.0 x 85.0 mm, 42 parts (3 on the bottom side), 88 nets.

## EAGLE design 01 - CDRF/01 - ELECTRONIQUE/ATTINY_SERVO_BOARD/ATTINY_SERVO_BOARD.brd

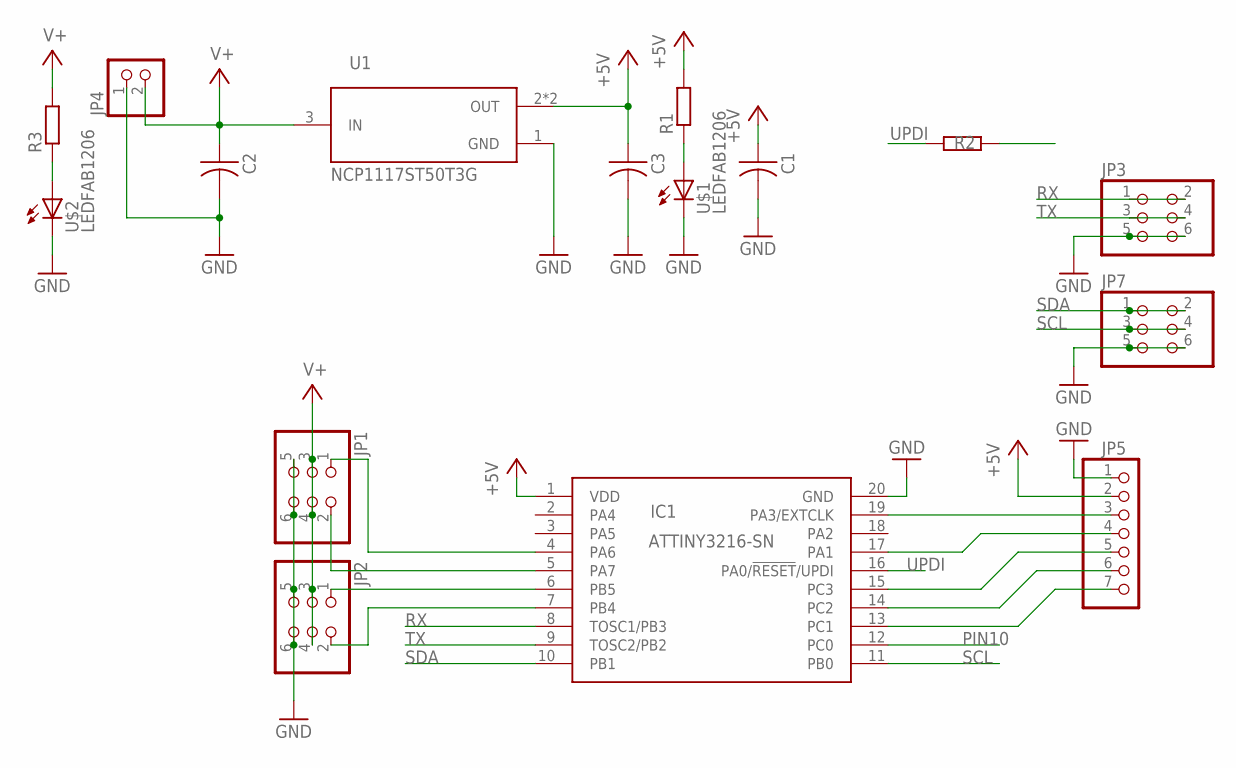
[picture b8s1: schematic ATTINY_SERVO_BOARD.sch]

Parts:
C1, C2, C3: CAP-US1206; C1206
IC1: ATTINY3216-SN; SOIC127P1030X265-20N
JP1, JP2, JP3, JP7: PINHD-2X03_2.54-SMD; 2X03SMD
JP4: PINHD-1X02_2.54-SMD-90°; 1X02SMD/90
JP5: PINHD-1X07_2.54-SMD-90°; 1X07SMD/90
R1, R2, R3: R-EU_R1206; R1206
U1: NCP1117ST50T3G; SOT230P700X180-4N
U$1, U$2: LEDFAB1206; LED1206FAB

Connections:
+5V: C1.1, C3.1, IC1.1 (VDD), JP5.2, R1.2, U1.2 (OUT), U1.4 (OUT)
GND: C1.2, C2.2, C3.2, IC1.20 (GND), JP1.5, JP1.6, JP2.5, JP2.6, JP3.5, JP3.6, JP4.1, JP5.1, JP7.5, JP7.6, U1.1 (GND), U$1.2 (C), U$2.2 (C)
unnamed: IC1.19 (PA3/EXTCLK), JP5.3
unnamed: R1.1, U$1.1 (A)
unnamed: IC1.7 (PB4), JP2.2
unnamed: IC1.6 (PB5), JP2.1
unnamed: IC1.5 (PA7), JP1.2
unnamed: IC1.4 (PA6), JP1.1
unnamed: R3.1, U$2.1 (A)
unnamed: IC1.17 (PA1), JP5.4
unnamed: IC1.15 (PC3), JP5.5
unnamed: IC1.14 (PC2), JP5.6
unnamed: IC1.13 (PC1), JP5.7
PIN10: IC1.12 (PC0)
RX: IC1.8 (TOSC1/PB3), JP3.1, JP3.2
SCL: IC1.11 (PB0), JP7.3, JP7.4
SDA: IC1.10 (PB1), JP7.1, JP7.2
TX: IC1.9 (TOSC2/PB2), JP3.3, JP3.4
UPDI: IC1.16 (PA0/!RESET!/UPDI), R2.2
V+: C2.1, JP1.3, JP1.4, JP2.3, JP2.4, JP4.2, R3.2, U1.3 (IN)

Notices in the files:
01 - CDRF/01 - ELECTRONIQUE/MAIN_BOARD V2/MAIN_BOARD_02.brd:
cc-by
